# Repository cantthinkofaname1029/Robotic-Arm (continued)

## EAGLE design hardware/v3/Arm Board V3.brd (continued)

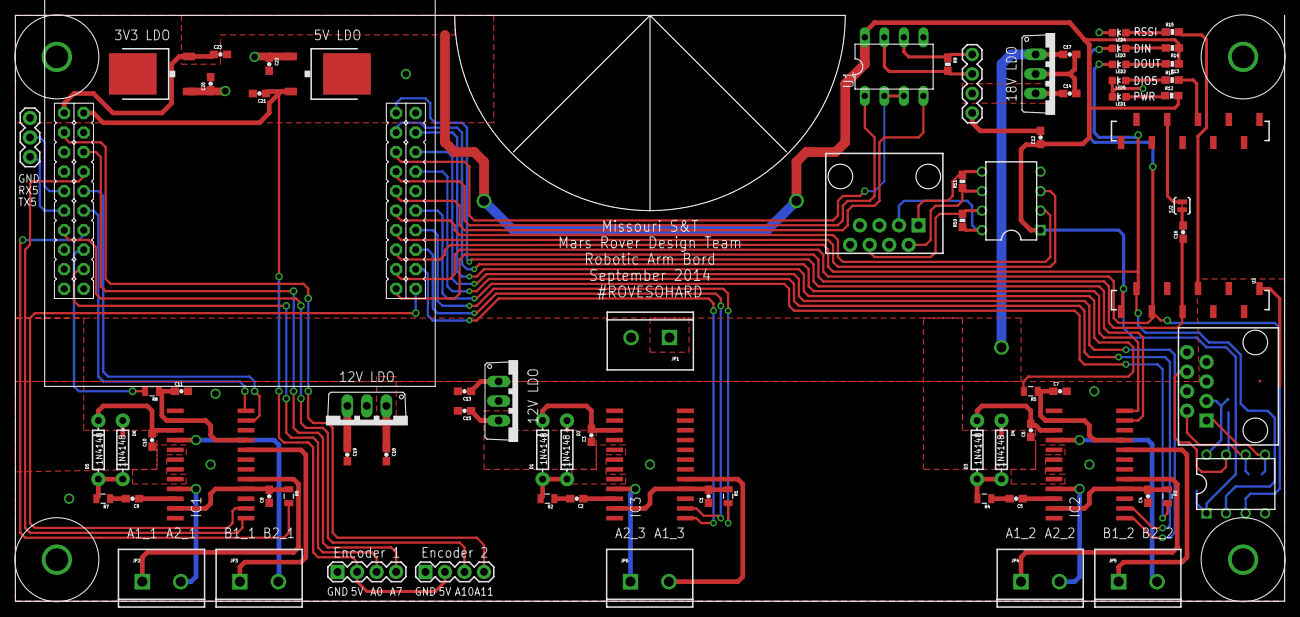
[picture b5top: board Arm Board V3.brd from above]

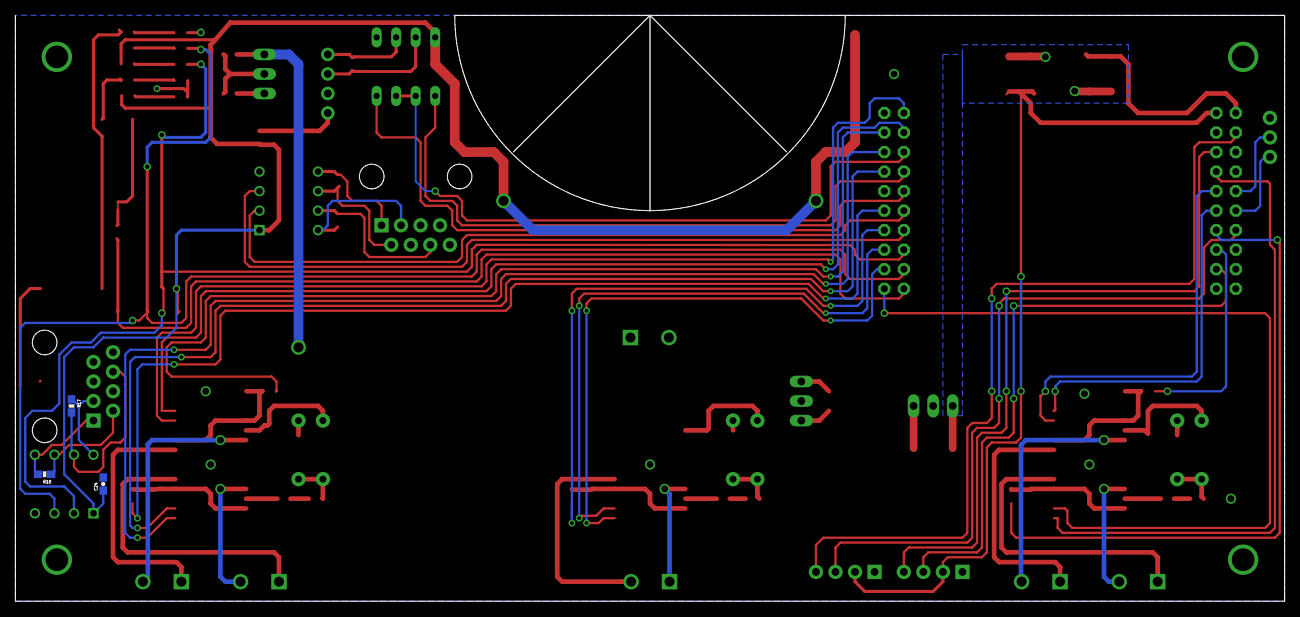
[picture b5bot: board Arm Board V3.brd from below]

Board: 2 copper layers, 165.1 x 76.2 mm, 83 parts (3 on the bottom side), 82 nets.

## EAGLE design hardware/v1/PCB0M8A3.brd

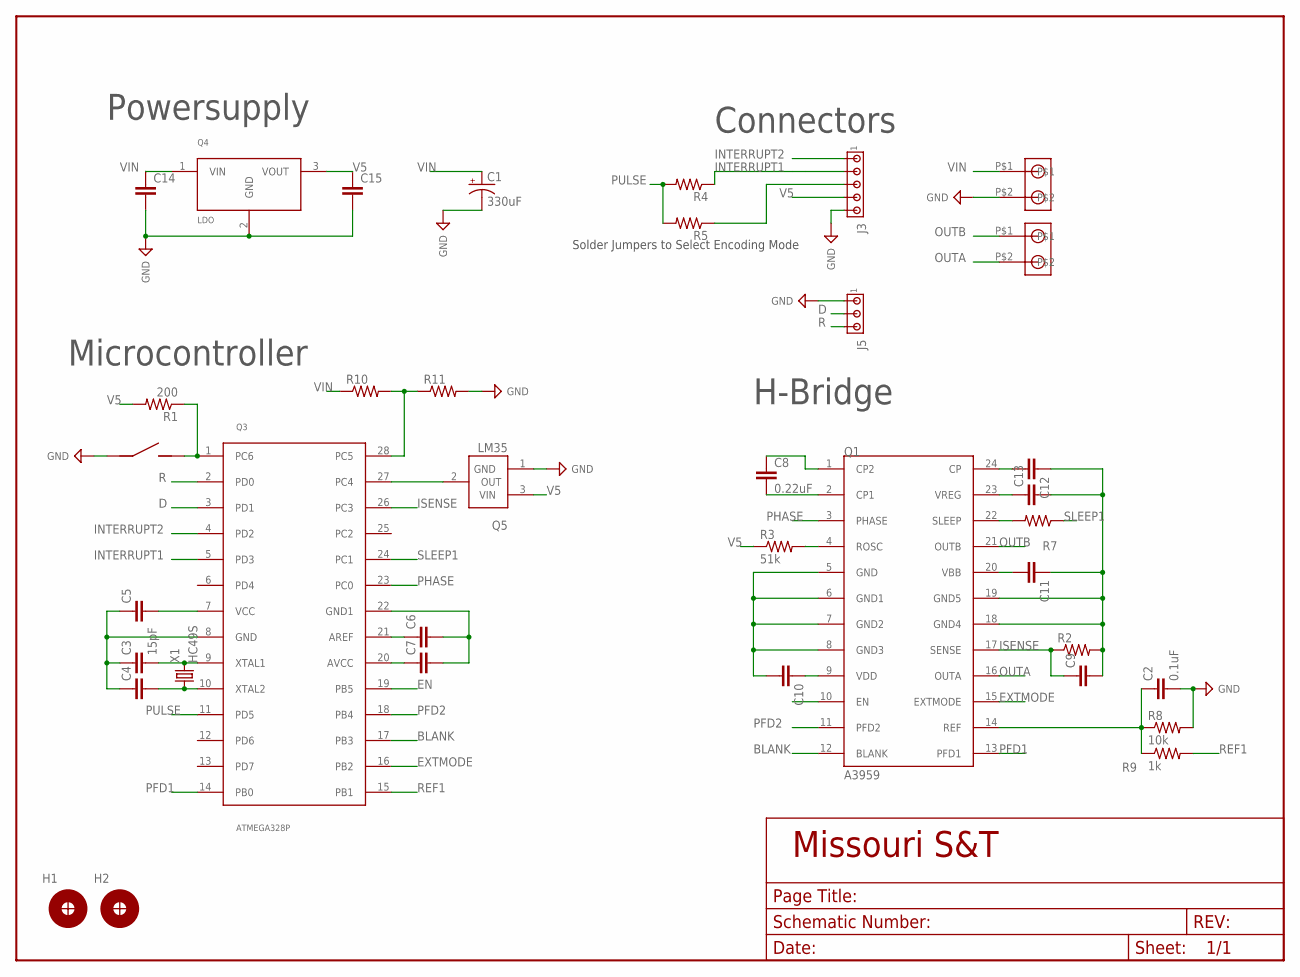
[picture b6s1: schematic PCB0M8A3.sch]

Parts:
C1: 330uF; C_8MM
C2: 0.1uF; C_0805
C3: 15pF; C_0805
C4, C5, C6, C7, C9, C10, C11, C12, C13, C14, C15: C_CAP_0805; C_0805
C8: 0.22uF; C_0805
H1, H2: H_MNTHOLE_#4
J1, J2: J_1546074-2282834-2; J_2.54MM
J3: J_MTA5P_100; J_MTA100_5P
J4: J_MC32857; J_TOGGLE
J5: J_MTA3P_100; J_MTA100_3P
Q1: A3959; DIP24
Q3: ATMEGA328P; DIP28
Q4: LDO; TO-220
Q5: LM35; TO-92-3
R1: 200; R_0805
R2: R_RES_2010; R_2010
R3: 51k; R_0805
R4, R5: R_RES_0603; R_0603
R7: R_1/4WL
R8: 10k; R_0805
R9: 1k; R_0805
R10, R11: R_RES_0805; R_0805
X1: HC49S; HC-49

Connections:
BLANK: Q1.12 (BLANK), Q3.17 (PB3)
D: J5.2, Q3.3 (PD1)
EN: Q1.10 (EN), Q3.19 (PB5)
EXTMODE: Q1.15 (EXTMODE), Q3.16 (PB2)
GND: C1.-, C2.2, C3.1, C4.1, C5.1, C6.2, C7.2, C9.2, C10.2, C11.1, C12.1, C13.2, C14.2, C15.2, J1.P$2, J3.5, J4.P$1 (1), J5.1, Q1.5 (GND), Q1.6 (GND1), Q1.7 (GND2), Q1.8 (GND3), Q1.18 (GND4), Q1.19 (GND5), Q3.8 (GND), Q3.22 (GND1), Q4.2 (GND), Q5.1 (GND), R2.2, R8.2, R11.2
INTERRUPT1: J3.2, Q3.5 (PD3), R4.1
INTERRUPT2: J3.1, Q3.4 (PD2)
ISENSE: C9.1, Q1.17 (SENSE), Q3.26 (PC3), R2.1
unnamed: C4.2, Q3.10 (XTAL2), X1.P$1 (1)
unnamed: C3.2, Q3.9 (XTAL1), X1.P$2 (2)
unnamed: Q1.22 (SLEEP), R7.2
unnamed: Q3.27 (PC4), Q5.2 (OUT)
unnamed: Q3.28 (PC5), R10.2, R11.1
unnamed: C6.1, Q3.21 (AREF)
unnamed: J3.3, R5.1
unnamed: J4.P$2 (2), Q3.1 (PC6), R1.1
unnamed: C8.1, Q1.1 (CP2)
unnamed: C8.2, Q1.2 (CP1)
unnamed: Q1.4 (ROSC), R3.2
unnamed: C12.2, Q1.24 (CP)
unnamed: C13.1, Q1.23 (VREG)
OUTA: J2.P$2, Q1.16 (OUTA)
OUTB: J2.P$1, Q1.21 (OUTB)
PFD1: Q1.13 (PFD1), Q3.14 (PB0)
PFD2: Q1.11 (PFD2), Q3.18 (PB4)
PHASE: Q1.3 (PHASE), Q3.23 (PC0)
PULSE: Q3.11 (PD5), R4.2, R5.2
R: J5.3, Q3.2 (PD0)
REF: C2.1, Q1.14 (REF), R8.1, R9.1
REF1: Q3.15 (PB1), R9.2
SLEEP1: Q3.24 (PC1), R7.1
V5: C5.2, C7.1, C10.1, C15.1, J3.4, Q1.9 (VDD), Q3.7 (VCC), Q3.20 (AVCC), Q4.3 (VOUT), Q5.3 (VIN), R1.2, R3.1
VIN: C1.+, C11.2, C14.1, J1.P$1, Q1.20 (VBB), Q4.1 (VIN), R10.1

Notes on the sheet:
Powersupply
Connectors
Microcontroller
H-Bridge
Solder Jumpers to Select Encoding Mode

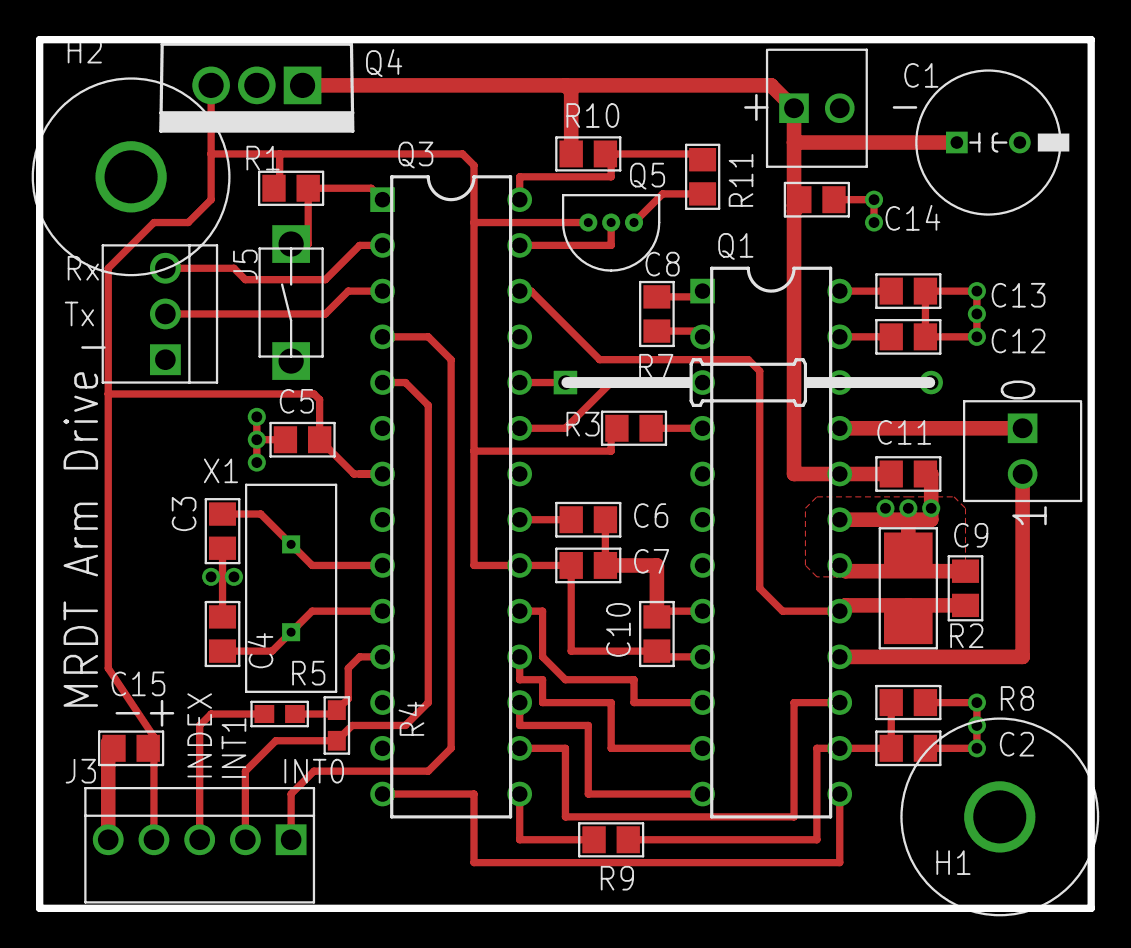
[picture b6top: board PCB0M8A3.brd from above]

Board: 2 copper layers, 58.4 x 48.3 mm, 37 parts (0 on the bottom side), 33 nets.

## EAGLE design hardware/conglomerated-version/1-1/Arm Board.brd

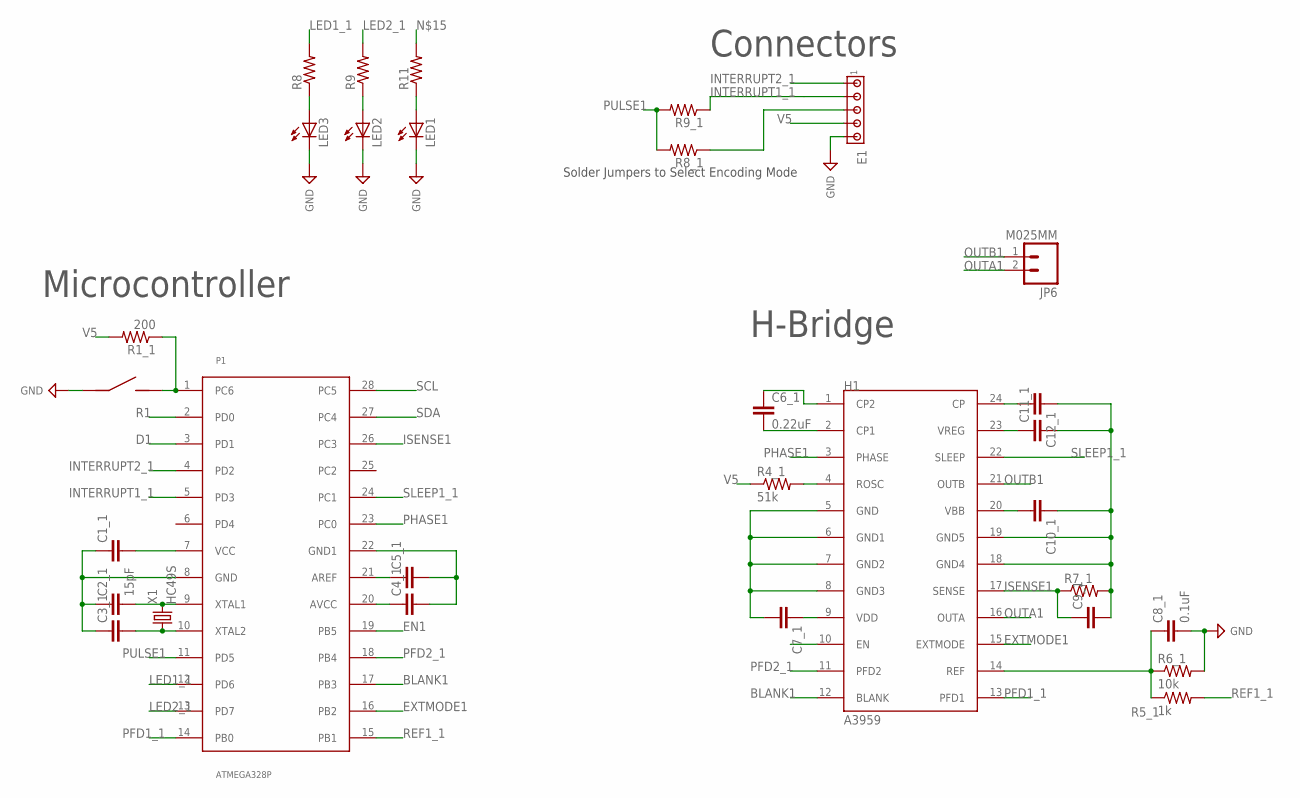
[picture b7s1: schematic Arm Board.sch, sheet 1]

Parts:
C1_1, C3_1, C4_1, C5_1, C7_1, C9_1, C10_1, C11_1, C12_1: C_CAP_0805; C_0805
C2_1: 15pF; C_0805
C6_1: 0.22uF; C_0805
C8_1: 0.1uF; C_0805
E1: J_MTA5P_100; J_MTA100_5P
H1: A3959; DIP24
JP6: M025MM; SCREWTERMINAL-5MM-2
LED1, LED2, LED3: LED1206; LED-1206
P1: ATMEGA328P; DIP28
R1_1: 200; R_0805
R4_1: 51k; R_0805
R5_1: 1k; R_0805
R6_1: 10k; R_0805
R7_1: R_RES_2010; R_2010
R8, R9, R11: RESISTOR1206; 1206
R8_1, R9_1: R_RES_0603; R_0603
S1: J_MC32857; J_TOGGLE
X1: HC49S; HC-49

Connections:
BLANK1: H1.12 (BLANK), P1.17 (PB3)
D1: P1.3 (PD1)
EN1: H1.10 (EN), P1.19 (PB5)
EXTMODE1: H1.15 (EXTMODE), P1.16 (PB2)
GND: C1_1.1, C2_1.1, C3_1.1, C4_1.2, C5_1.2, C7_1.2, C8_1.2, C9_1.2, C10_1.1, C11_1.2, C12_1.1, E1.5, H1.5 (GND), H1.6 (GND1), H1.7 (GND2), H1.8 (GND3), H1.18 (GND4), H1.19 (GND5), LED1.C, LED2.C, LED3.C, P1.8 (GND), P1.22 (GND1), R6_1.2, R7_1.2, S1.P$1 (1); also elsewhere on the board
INTERRUPT1_1: E1.2, P1.5 (PD3), R9_1.1
INTERRUPT2_1: E1.1, P1.4 (PD2)
ISENSE1: C9_1.1, H1.17 (SENSE), P1.26 (PC3), R7_1.1
LED1_1: P1.12 (PD6), R8.2
LED2_1: P1.13 (PD7), R9.2
unnamed: LED3.A, R8.1
unnamed: LED2.A, R9.1
unnamed: LED1.A, R11.1
unnamed: C3_1.2, P1.10 (XTAL2), X1.P$1 (1)
unnamed: C2_1.2, P1.9 (XTAL1), X1.P$2 (2)
unnamed: C5_1.1, P1.21 (AREF)
unnamed: P1.1 (PC6), R1_1.1, R11.2, S1.P$2 (2)
unnamed: C6_1.1, H1.1 (CP2)
unnamed: C6_1.2, H1.2 (CP1)
unnamed: H1.4 (ROSC), R4_1.2
unnamed: C12_1.2, H1.24 (CP)
unnamed: C11_1.1, H1.23 (VREG)
unnamed: E1.3, R8_1.1
OUTA1: H1.16 (OUTA), JP6.2
OUTB1: H1.21 (OUTB), JP6.1
PFD1_1: H1.13 (PFD1), P1.14 (PB0)
PFD2_1: H1.11 (PFD2), P1.18 (PB4)
PHASE1: H1.3 (PHASE), P1.23 (PC0)
PULSE1: P1.11 (PD5), R8_1.2, R9_1.2
R1: P1.2 (PD0)
REF1: C8_1.1, H1.14 (REF), R5_1.1, R6_1.1
REF1_1: P1.15 (PB1), R5_1.2
SCL: P1.28 (PC5); also elsewhere on the board
SDA: P1.27 (PC4); also elsewhere on the board
SLEEP1_1: H1.22 (SLEEP), P1.24 (PC1)
V5: C1_1.2, C4_1.1, C7_1.1, E1.4, H1.9 (VDD), P1.7 (VCC), P1.20 (AVCC), R1_1.2, R4_1.1; also elsewhere on the board
VIN: C10_1.2, H1.20 (VBB); also elsewhere on the board

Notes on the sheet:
Connectors
Microcontroller
H-Bridge
Solder Jumpers to Select Encoding Mode

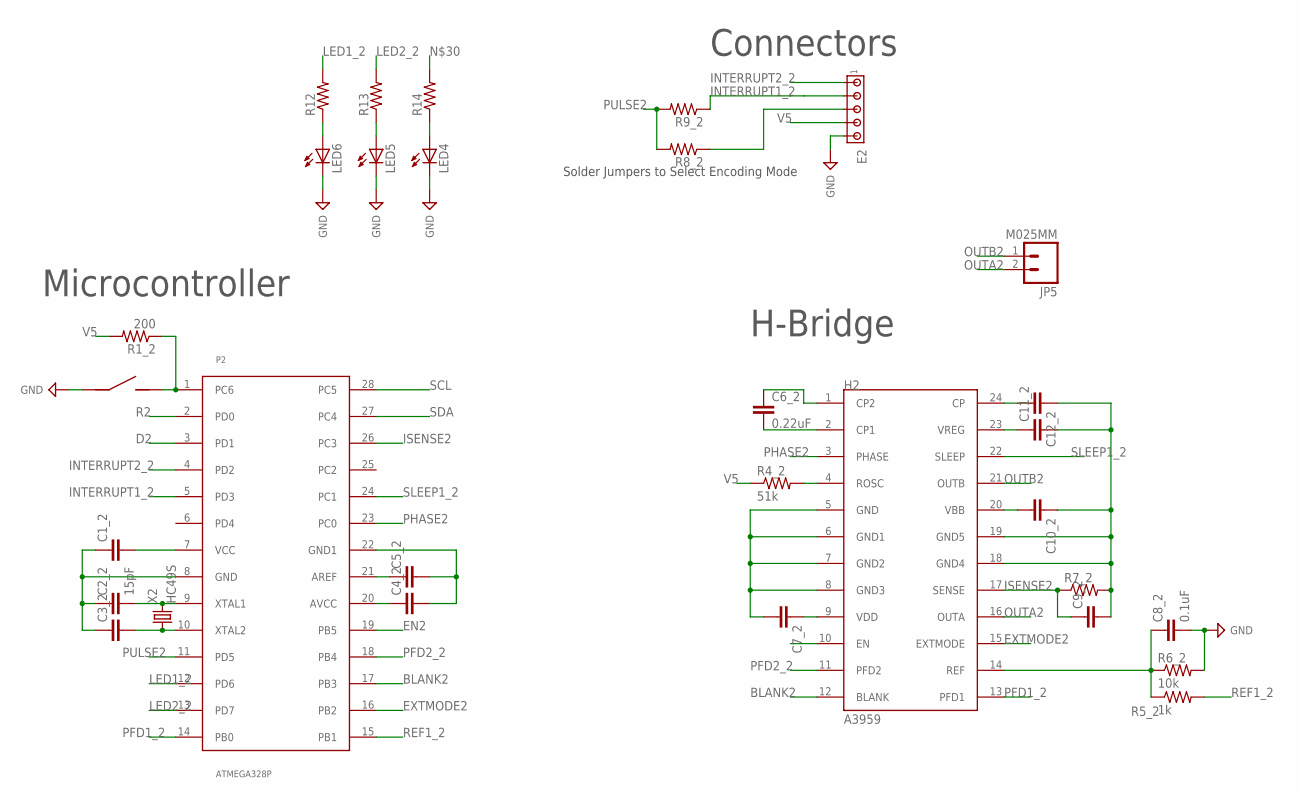
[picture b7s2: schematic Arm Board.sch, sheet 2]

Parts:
C1_2, C3_2, C4_2, C5_2, C7_2, C9_2, C10_2, C11_2, C12_2: C_CAP_0805; C_0805
C2_2: 15pF; C_0805
C6_2: 0.22uF; C_0805
C8_2: 0.1uF; C_0805
E2: J_MTA5P_100; J_MTA100_5P
H2: A3959; DIP24
JP5: M025MM; SCREWTERMINAL-5MM-2
LED4, LED5, LED6: LED1206; LED-1206
P2: ATMEGA328P; DIP28
R1_2: 200; R_0805
R4_2: 51k; R_0805
R5_2: 1k; R_0805
R6_2: 10k; R_0805
R7_2: R_RES_2010; R_2010
R8_2, R9_2: R_RES_0603; R_0603
R12, R13, R14: RESISTOR1206; 1206
S2: J_MC32857; J_TOGGLE
X2: HC49S; HC-49

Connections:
BLANK2: H2.12 (BLANK), P2.17 (PB3)
D2: P2.3 (PD1)
EN2: H2.10 (EN), P2.19 (PB5)
EXTMODE2: H2.15 (EXTMODE), P2.16 (PB2)
GND: C1_2.1, C2_2.1, C3_2.1, C4_2.2, C5_2.2, C7_2.2, C8_2.2, C9_2.2, C10_2.1, C11_2.2, C12_2.1, E2.5, H2.5 (GND), H2.6 (GND1), H2.7 (GND2), H2.8 (GND3), H2.18 (GND4), H2.19 (GND5), LED4.C, LED5.C, LED6.C, P2.8 (GND), P2.22 (GND1), R6_2.2, R7_2.2, S2.P$1 (1); also elsewhere on the board
INTERRUPT1_2: E2.2, P2.5 (PD3), R9_2.1
INTERRUPT2_2: E2.1, P2.4 (PD2)
ISENSE2: C9_2.1, H2.17 (SENSE), P2.26 (PC3), R7_2.1
LED1_2: P2.12 (PD6), R12.2
LED2_2: P2.13 (PD7), R13.2
unnamed: LED6.A, R12.1
unnamed: LED5.A, R13.1
unnamed: LED4.A, R14.1
unnamed: C3_2.2, P2.10 (XTAL2), X2.P$1 (1)
unnamed: C2_2.2, P2.9 (XTAL1), X2.P$2 (2)
unnamed: C5_2.1, P2.21 (AREF)
unnamed: P2.1 (PC6), R1_2.1, R14.2, S2.P$2 (2)
unnamed: C6_2.1, H2.1 (CP2)
unnamed: C6_2.2, H2.2 (CP1)
unnamed: H2.4 (ROSC), R4_2.2
unnamed: C12_2.2, H2.24 (CP)
unnamed: C11_2.1, H2.23 (VREG)
unnamed: E2.3, R8_2.1
OUTA2: H2.16 (OUTA), JP5.2
OUTB2: H2.21 (OUTB), JP5.1
PFD1_2: H2.13 (PFD1), P2.14 (PB0)
PFD2_2: H2.11 (PFD2), P2.18 (PB4)
PHASE2: H2.3 (PHASE), P2.23 (PC0)
PULSE2: P2.11 (PD5), R8_2.2, R9_2.2
R2: P2.2 (PD0)
REF1_2: P2.15 (PB1), R5_2.2
REF2: C8_2.1, H2.14 (REF), R5_2.1, R6_2.1
SCL: P2.28 (PC5); also elsewhere on the board
SDA: P2.27 (PC4); also elsewhere on the board
SLEEP1_2: H2.22 (SLEEP), P2.24 (PC1)
V5: C1_2.2, C4_2.1, C7_2.1, E2.4, H2.9 (VDD), P2.7 (VCC), P2.20 (AVCC), R1_2.2, R4_2.1; also elsewhere on the board
VIN: C10_2.2, H2.20 (VBB); also elsewhere on the board

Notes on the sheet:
Connectors
Microcontroller
H-Bridge
Solder Jumpers to Select Encoding Mode

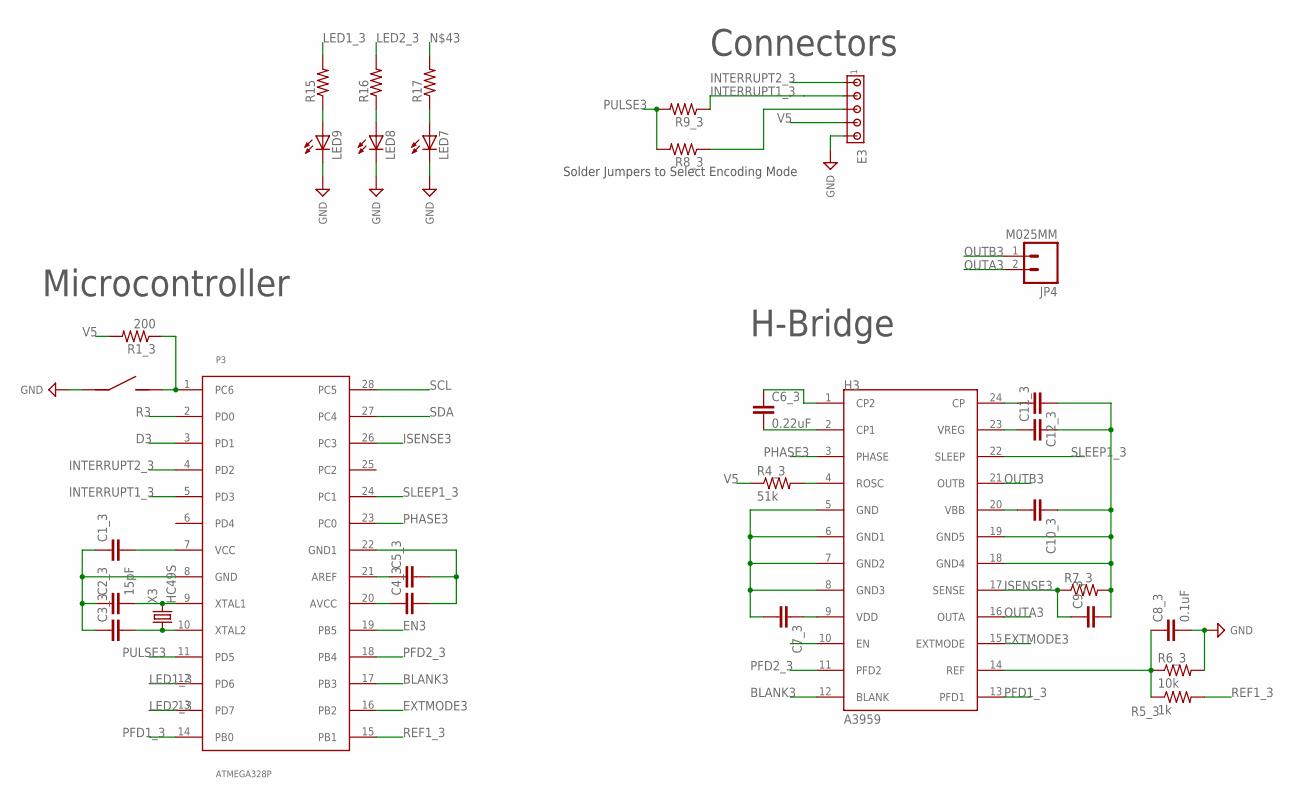
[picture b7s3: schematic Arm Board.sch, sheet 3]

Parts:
C1_3, C3_3, C4_3, C5_3, C7_3, C9_3, C10_3, C11_3, C12_3: C_CAP_0805; C_0805
C2_3: 15pF; C_0805
C6_3: 0.22uF; C_0805
C8_3: 0.1uF; C_0805
E3: J_MTA5P_100; J_MTA100_5P
H3: A3959; DIP24
JP4: M025MM; SCREWTERMINAL-5MM-2
LED7, LED8, LED9: LED1206; LED-1206
P3: ATMEGA328P; DIP28
R1_3: 200; R_0805
R4_3: 51k; R_0805
R5_3: 1k; R_0805
R6_3: 10k; R_0805
R7_3: R_RES_2010; R_2010
R8_3, R9_3: R_RES_0603; R_0603
R15, R16, R17: RESISTOR1206; 1206
S3: J_MC32857; J_TOGGLE
X3: HC49S; HC-49

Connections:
BLANK3: H3.12 (BLANK), P3.17 (PB3)
D3: P3.3 (PD1)
EN3: H3.10 (EN), P3.19 (PB5)
EXTMODE3: H3.15 (EXTMODE), P3.16 (PB2)
GND: C1_3.1, C2_3.1, C3_3.1, C4_3.2, C5_3.2, C7_3.2, C8_3.2, C9_3.2, C10_3.1, C11_3.2, C12_3.1, E3.5, H3.5 (GND), H3.6 (GND1), H3.7 (GND2), H3.8 (GND3), H3.18 (GND4), H3.19 (GND5), LED7.C, LED8.C, LED9.C, P3.8 (GND), P3.22 (GND1), R6_3.2, R7_3.2, S3.P$1 (1); also elsewhere on the board
INTERRUPT1_3: E3.2, P3.5 (PD3), R9_3.1
INTERRUPT2_3: E3.1, P3.4 (PD2)
ISENSE3: C9_3.1, H3.17 (SENSE), P3.26 (PC3), R7_3.1
LED1_3: P3.12 (PD6), R15.2
LED2_3: P3.13 (PD7), R16.2
unnamed: LED9.A, R15.1
unnamed: LED8.A, R16.1
unnamed: LED7.A, R17.1
unnamed: C3_3.2, P3.10 (XTAL2), X3.P$1 (1)
unnamed: C2_3.2, P3.9 (XTAL1), X3.P$2 (2)
unnamed: C5_3.1, P3.21 (AREF)
unnamed: P3.1 (PC6), R1_3.1, R17.2, S3.P$2 (2)
unnamed: C6_3.1, H3.1 (CP2)
unnamed: C6_3.2, H3.2 (CP1)
unnamed: H3.4 (ROSC), R4_3.2
unnamed: C12_3.2, H3.24 (CP)
unnamed: C11_3.1, H3.23 (VREG)
unnamed: E3.3, R8_3.1
OUTA3: H3.16 (OUTA), JP4.2
OUTB3: H3.21 (OUTB), JP4.1
PFD1_3: H3.13 (PFD1), P3.14 (PB0)
PFD2_3: H3.11 (PFD2), P3.18 (PB4)
PHASE3: H3.3 (PHASE), P3.23 (PC0)
PULSE3: P3.11 (PD5), R8_3.2, R9_3.2
R3: P3.2 (PD0)
REF1_3: P3.15 (PB1), R5_3.2
REF3: C8_3.1, H3.14 (REF), R5_3.1, R6_3.1
SCL: P3.28 (PC5); also elsewhere on the board
SDA: P3.27 (PC4); also elsewhere on the board
SLEEP1_3: H3.22 (SLEEP), P3.24 (PC1)
V5: C1_3.2, C4_3.1, C7_3.1, E3.4, H3.9 (VDD), P3.7 (VCC), P3.20 (AVCC), R1_3.2, R4_3.1; also elsewhere on the board
VIN: C10_3.2, H3.20 (VBB); also elsewhere on the board

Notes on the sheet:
Connectors
Microcontroller
H-Bridge
Solder Jumpers to Select Encoding Mode

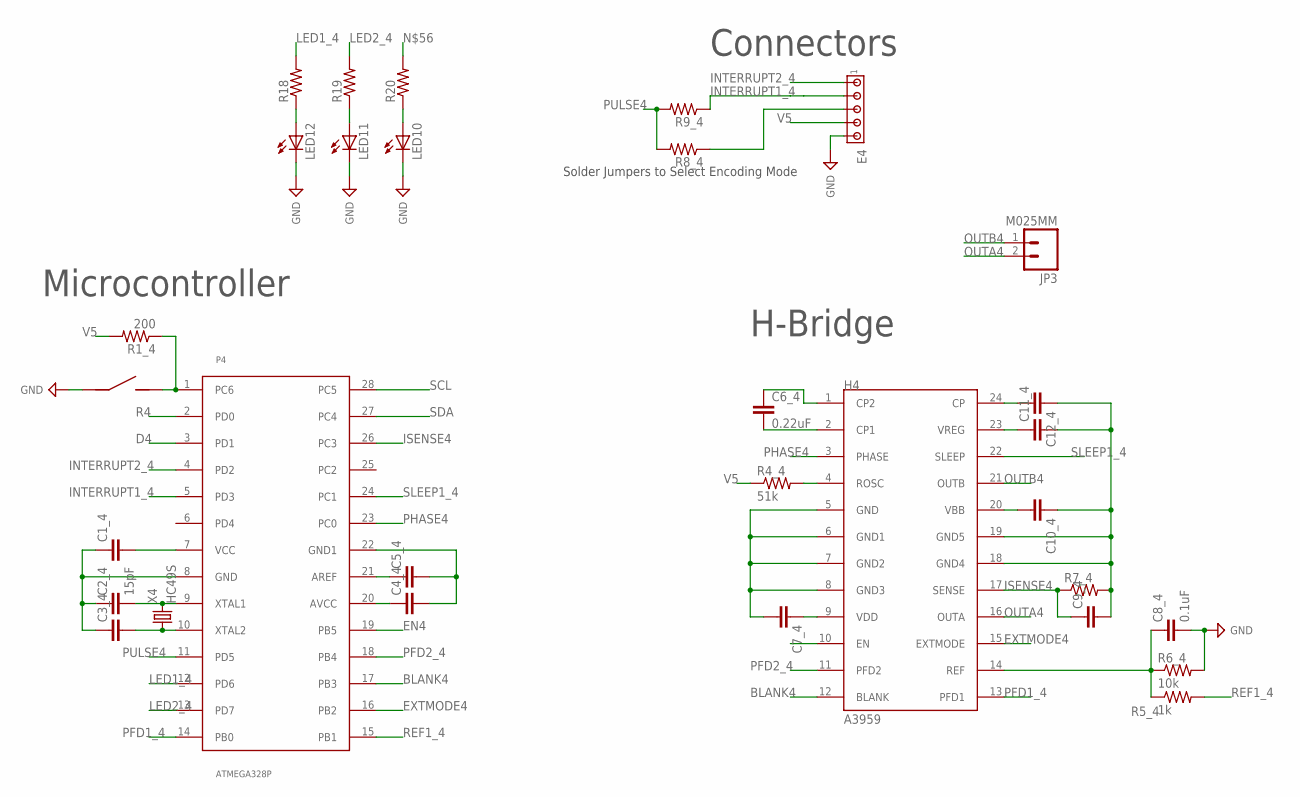
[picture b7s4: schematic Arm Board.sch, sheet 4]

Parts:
C1_4, C3_4, C4_4, C5_4, C7_4, C9_4, C10_4, C11_4, C12_4: C_CAP_0805; C_0805
C2_4: 15pF; C_0805
C6_4: 0.22uF; C_0805
C8_4: 0.1uF; C_0805
E4: J_MTA5P_100; J_MTA100_5P
H4: A3959; DIP24
JP3: M025MM; SCREWTERMINAL-5MM-2
LED10, LED11, LED12: LED1206; LED-1206
P4: ATMEGA328P; DIP28
R1_4: 200; R_0805
R4_4: 51k; R_0805
R5_4: 1k; R_0805
R6_4: 10k; R_0805
R7_4: R_RES_2010; R_2010
R8_4, R9_4: R_RES_0603; R_0603
R18, R19, R20: RESISTOR1206; 1206
S4: J_MC32857; J_TOGGLE
X4: HC49S; HC-49

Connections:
BLANK4: H4.12 (BLANK), P4.17 (PB3)
D4: P4.3 (PD1)
EN4: H4.10 (EN), P4.19 (PB5)
EXTMODE4: H4.15 (EXTMODE), P4.16 (PB2)
GND: C1_4.1, C2_4.1, C3_4.1, C4_4.2, C5_4.2, C7_4.2, C8_4.2, C9_4.2, C10_4.1, C11_4.2, C12_4.1, E4.5, H4.5 (GND), H4.6 (GND1), H4.7 (GND2), H4.8 (GND3), H4.18 (GND4), H4.19 (GND5), LED10.C, LED11.C, LED12.C, P4.8 (GND), P4.22 (GND1), R6_4.2, R7_4.2, S4.P$1 (1); also elsewhere on the board
INTERRUPT1_4: E4.2, P4.5 (PD3), R9_4.1
INTERRUPT2_4: E4.1, P4.4 (PD2)
ISENSE4: C9_4.1, H4.17 (SENSE), P4.26 (PC3), R7_4.1
LED1_4: P4.12 (PD6), R18.2
LED2_4: P4.13 (PD7), R19.2
unnamed: LED12.A, R18.1
unnamed: LED11.A, R19.1
unnamed: LED10.A, R20.1
unnamed: C3_4.2, P4.10 (XTAL2), X4.P$1 (1)
unnamed: C2_4.2, P4.9 (XTAL1), X4.P$2 (2)
unnamed: C5_4.1, P4.21 (AREF)
unnamed: P4.1 (PC6), R1_4.1, R20.2, S4.P$2 (2)
unnamed: C6_4.1, H4.1 (CP2)
unnamed: C6_4.2, H4.2 (CP1)
unnamed: H4.4 (ROSC), R4_4.2
unnamed: C12_4.2, H4.24 (CP)
unnamed: C11_4.1, H4.23 (VREG)
unnamed: E4.3, R8_4.1
OUTA4: H4.16 (OUTA), JP3.2
OUTB4: H4.21 (OUTB), JP3.1
PFD1_4: H4.13 (PFD1), P4.14 (PB0)
PFD2_4: H4.11 (PFD2), P4.18 (PB4)
PHASE4: H4.3 (PHASE), P4.23 (PC0)
PULSE4: P4.11 (PD5), R8_4.2, R9_4.2
R4: P4.2 (PD0)
REF1_4: P4.15 (PB1), R5_4.2
REF4: C8_4.1, H4.14 (REF), R5_4.1, R6_4.1
SCL: P4.28 (PC5); also elsewhere on the board
SDA: P4.27 (PC4); also elsewhere on the board
SLEEP1_4: H4.22 (SLEEP), P4.24 (PC1)
V5: C1_4.2, C4_4.1, C7_4.1, E4.4, H4.9 (VDD), P4.7 (VCC), P4.20 (AVCC), R1_4.2, R4_4.1; also elsewhere on the board
VIN: C10_4.2, H4.20 (VBB); also elsewhere on the board

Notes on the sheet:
Connectors
Microcontroller
H-Bridge
Solder Jumpers to Select Encoding Mode

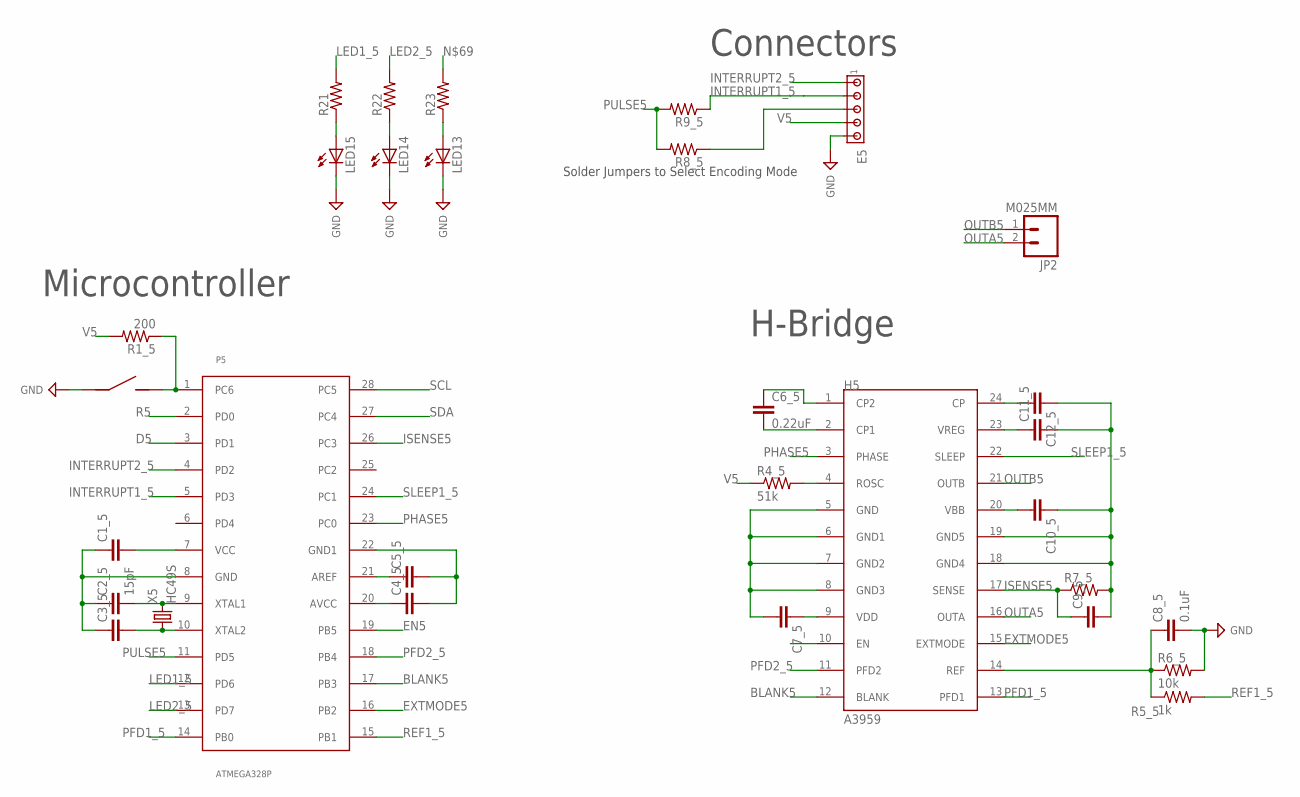
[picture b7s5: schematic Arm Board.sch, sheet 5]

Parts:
C1_5, C3_5, C4_5, C5_5, C7_5, C9_5, C10_5, C11_5, C12_5: C_CAP_0805; C_0805
C2_5: 15pF; C_0805
C6_5: 0.22uF; C_0805
C8_5: 0.1uF; C_0805
E5: J_MTA5P_100; J_MTA100_5P
H5: A3959; DIP24
JP2: M025MM; SCREWTERMINAL-5MM-2
LED13, LED14, LED15: LED1206; LED-1206
P5: ATMEGA328P; DIP28
R1_5: 200; R_0805
R4_5: 51k; R_0805
R5_5: 1k; R_0805
R6_5: 10k; R_0805
R7_5: R_RES_2010; R_2010
R8_5, R9_5: R_RES_0603; R_0603
R21, R22, R23: RESISTOR1206; 1206
S5: J_MC32857; J_TOGGLE
X5: HC49S; HC-49

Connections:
BLANK5: H5.12 (BLANK), P5.17 (PB3)
D5: P5.3 (PD1)
EN5: H5.10 (EN), P5.19 (PB5)
EXTMODE5: H5.15 (EXTMODE), P5.16 (PB2)
GND: C1_5.1, C2_5.1, C3_5.1, C4_5.2, C5_5.2, C7_5.2, C8_5.2, C9_5.2, C10_5.1, C11_5.2, C12_5.1, E5.5, H5.5 (GND), H5.6 (GND1), H5.7 (GND2), H5.8 (GND3), H5.18 (GND4), H5.19 (GND5), LED13.C, LED14.C, LED15.C, P5.8 (GND), P5.22 (GND1), R6_5.2, R7_5.2, S5.P$1 (1); also elsewhere on the board
INTERRUPT1_5: E5.2, P5.5 (PD3), R9_5.1
INTERRUPT2_5: E5.1, P5.4 (PD2)
ISENSE5: C9_5.1, H5.17 (SENSE), P5.26 (PC3), R7_5.1
LED1_5: P5.12 (PD6), R21.2
LED2_5: P5.13 (PD7), R22.2
unnamed: LED15.A, R21.1
unnamed: LED14.A, R22.1
unnamed: LED13.A, R23.1
unnamed: C3_5.2, P5.10 (XTAL2), X5.P$1 (1)
unnamed: C2_5.2, P5.9 (XTAL1), X5.P$2 (2)
unnamed: C5_5.1, P5.21 (AREF)
unnamed: P5.1 (PC6), R1_5.1, R23.2, S5.P$2 (2)
unnamed: C6_5.1, H5.1 (CP2)
unnamed: C6_5.2, H5.2 (CP1)
unnamed: H5.4 (ROSC), R4_5.2
unnamed: C12_5.2, H5.24 (CP)
unnamed: C11_5.1, H5.23 (VREG)
unnamed: E5.3, R8_5.1
OUTA5: H5.16 (OUTA), JP2.2
OUTB5: H5.21 (OUTB), JP2.1
PFD1_5: H5.13 (PFD1), P5.14 (PB0)
PFD2_5: H5.11 (PFD2), P5.18 (PB4)
PHASE5: H5.3 (PHASE), P5.23 (PC0)
PULSE5: P5.11 (PD5), R8_5.2, R9_5.2
R5: P5.2 (PD0)
REF1_5: P5.15 (PB1), R5_5.2
REF5: C8_5.1, H5.14 (REF), R5_5.1, R6_5.1
SCL: P5.28 (PC5); also elsewhere on the board
SDA: P5.27 (PC4); also elsewhere on the board
SLEEP1_5: H5.22 (SLEEP), P5.24 (PC1)
V5: C1_5.2, C4_5.1, C7_5.1, E5.4, H5.9 (VDD), P5.7 (VCC), P5.20 (AVCC), R1_5.2, R4_5.1; also elsewhere on the board
VIN: C10_5.2, H5.20 (VBB); also elsewhere on the board

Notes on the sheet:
Connectors
Microcontroller
H-Bridge
Solder Jumpers to Select Encoding Mode

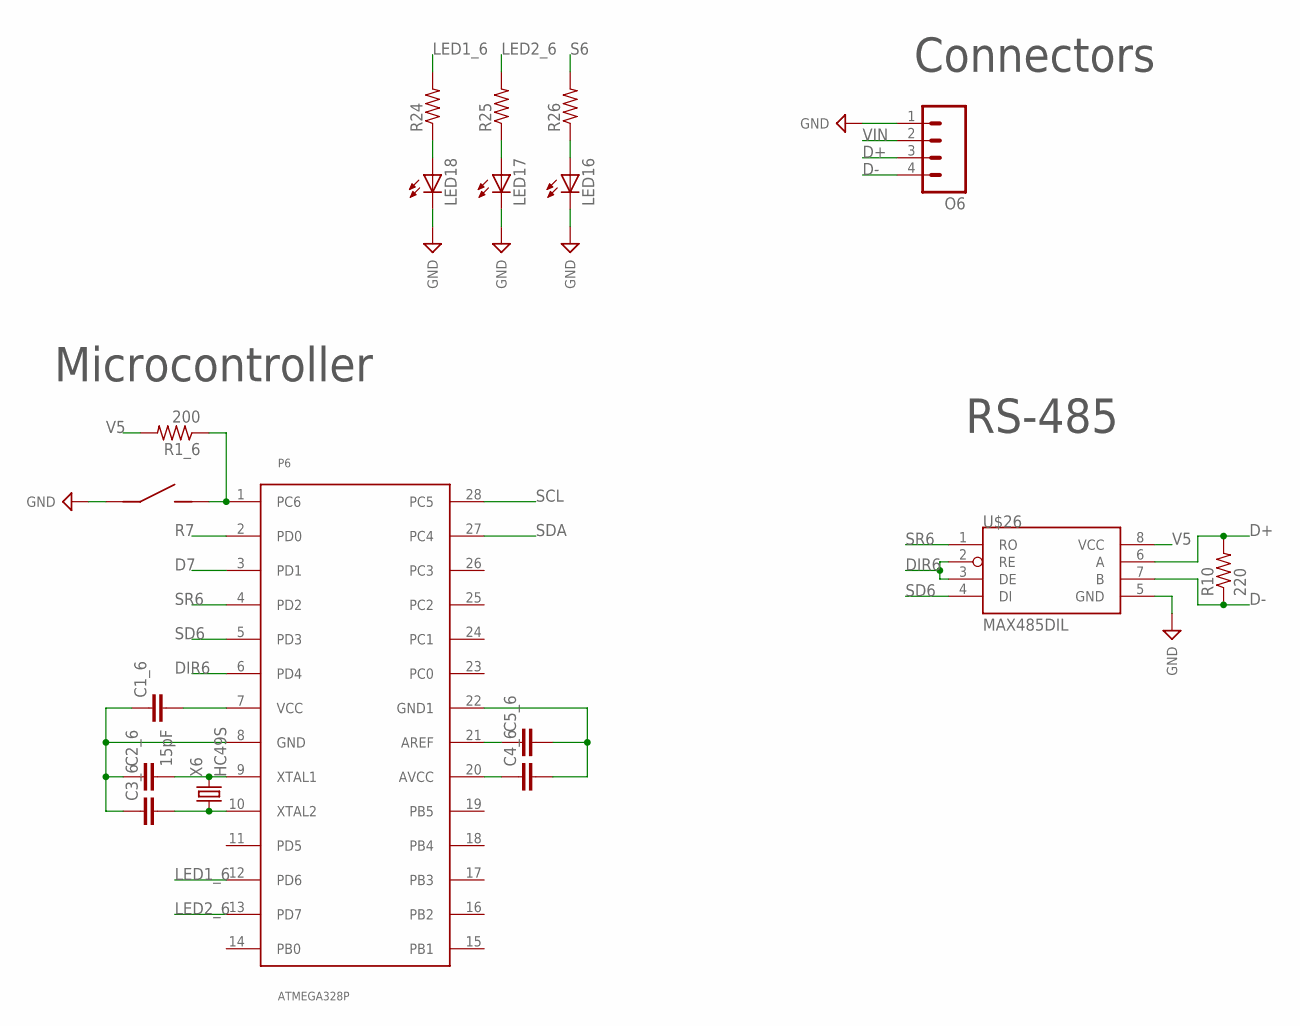
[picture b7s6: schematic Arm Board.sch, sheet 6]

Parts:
C1_6, C3_6, C4_6, C5_6: C_CAP_0805; C_0805
C2_6: 15pF; C_0805
J6: J_MC32857; J_TOGGLE
LED16, LED17, LED18: LED1206; LED-1206
O6: M041X04_NO_SILK; 1X04_NO_SILK
P6: ATMEGA328P; DIP28
R1_6: 200; R_0805
R10: 220; AXIAL-0.3EZ
R24, R25, R26: RESISTOR1206; 1206
U$26: MAX485DIL; DIL08
X6: HC49S; HC-49

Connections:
D7: P6.3 (PD1)
D+: O6.3, R10.P$2 (2), U$26.6 (A)
D-: O6.4, R10.P$1 (1), U$26.7 (B)
DIR6: P6.6 (PD4), U$26.2 (RE), U$26.3 (DE)
GND: C1_6.1, C2_6.1, C3_6.1, C4_6.2, C5_6.2, J6.P$1 (1), LED16.C, LED17.C, LED18.C, O6.1, P6.8 (GND), P6.22 (GND1), U$26.5 (GND); also elsewhere on the board
LED1_6: P6.12 (PD6), R24.2
LED2_6: P6.13 (PD7), R25.2
unnamed: LED18.A, R24.1
unnamed: LED17.A, R25.1
unnamed: LED16.A, R26.1
unnamed: C3_6.2, P6.10 (XTAL2), X6.P$1 (1)
unnamed: C2_6.2, P6.9 (XTAL1), X6.P$2 (2)
unnamed: C5_6.1, P6.21 (AREF)
R7: P6.2 (PD0)
S6: J6.P$2 (2), P6.1 (PC6), R1_6.1, R26.2
SCL: P6.28 (PC5); also elsewhere on the board
SD6: P6.5 (PD3), U$26.4 (DI)
SDA: P6.27 (PC4); also elsewhere on the board
SR6: P6.4 (PD2), U$26.1 (RO)
V5: C1_6.2, C4_6.1, P6.7 (VCC), P6.20 (AVCC), R1_6.2, U$26.8 (VCC); also elsewhere on the board
VIN: O6.2; also elsewhere on the board

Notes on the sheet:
Connectors
Microcontroller
RS-485

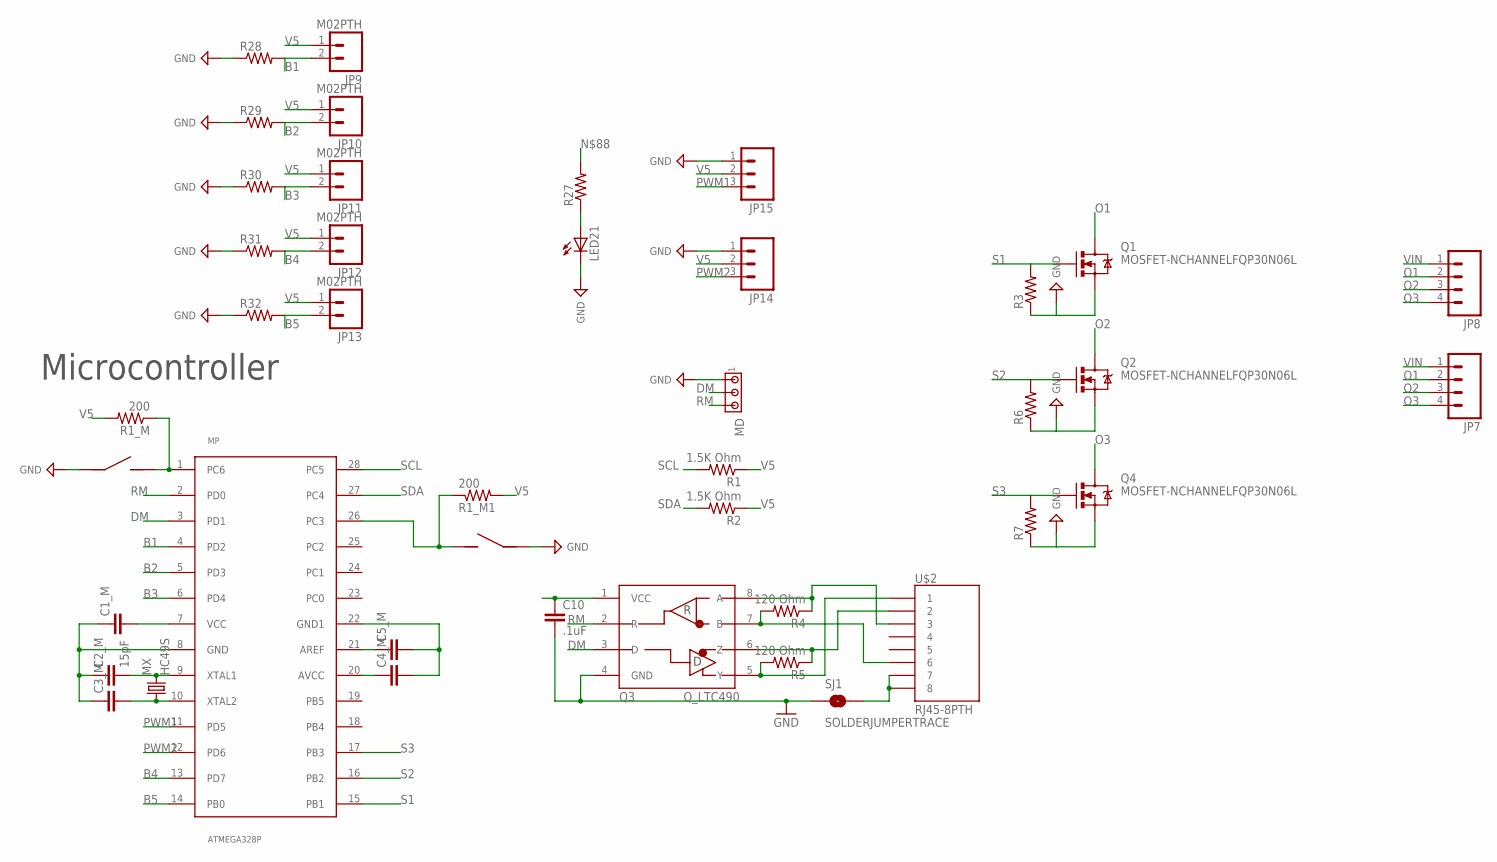
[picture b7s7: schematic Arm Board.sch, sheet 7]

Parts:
C1_M, C3_M, C4_M, C5_M: C_CAP_0805; C_0805
C2_M: 15pF; C_0805
C10: .1uF; CAP-PTH-SMALL-KIT
JP7, JP8: M041X04_NO_SILK; 1X04_NO_SILK
JP9, JP10, JP11, JP12, JP13: M02PTH; 1X02
JP14, JP15: M03PTH; 1X03
LED21: LED1206; LED-1206
MD: J_MTA3P_100; J_MTA100_3P
MP: ATMEGA328P; DIP28
MS, MS1: J_MC32857; J_TOGGLE
MX: HC49S; HC-49
Q1, Q2, Q4: MOSFET-NCHANNELFQP30N06L; TO220V
Q3: Q_LTC490; DIP8
R1, R2: 1.5K Ohm; AXIAL-0.3
R1_M, R1_M1: 200; R_0805
R3, R6, R7: 10KOHM1/6W5%(PTH)KIT; AXIAL-0.3-KIT
R4, R5: 120 Ohm; AXIAL-0.3
R27: RESISTOR1206; 1206
R28, R29, R30, R31, R32: RESISTORPTH-1/6W; 1/6W-RES
SJ1: SOLDERJUMPERTRACE; SJ_2S-TRACE
U$2: RJ45-8PTH; RJ45-8

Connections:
B1: JP9.2, MP.4 (PD2), R28.2
B2: JP10.2, MP.5 (PD3), R29.2
B3: JP11.2, MP.6 (PD4), R30.2
B4: JP12.2, MP.13 (PD7), R31.2
B5: JP13.2, MP.14 (PB0), R32.2
DM: MD.2, MP.3 (PD1), Q3.3 (D)
GND: C1_M.1, C2_M.1, C3_M.1, C4_M.2, C5_M.2, C10.2, JP14.1, JP15.1, LED21.C, MD.1, MP.8 (GND), MP.22 (GND1), MS.P$1 (1), MS1.P$1 (1), Q1.3 (S), Q2.3 (S), Q3.4 (GND), Q4.3 (S), R3.P$1 (1), R6.P$1 (1), R7.P$1 (1), R28.1, R29.1, R30.1, R31.1, R32.1, SJ1.1; also elsewhere on the board
unnamed: Q3.8 (A), R4.P$1 (1), U$2.3
unnamed: Q3.5 (Y), R5.P$2 (2), U$2.1
unnamed: SJ1.2, U$2.7, U$2.8
unnamed: Q3.6 (Z), R5.P$1 (1), U$2.2
unnamed: Q3.7 (B), R4.P$2 (2), U$2.6
unnamed: LED21.A, R27.1
unnamed: MP.26 (PC3), MS1.P$2 (2), R1_M1.1
unnamed: C3_M.2, MP.10 (XTAL2), MX.P$1 (1)
unnamed: C2_M.2, MP.9 (XTAL1), MX.P$2 (2)
unnamed: C5_M.1, MP.21 (AREF)
unnamed: MP.1 (PC6), MS.P$2 (2), R1_M.1, R27.2
O1: JP7.2, JP8.2, Q1.2 (D)
O2: JP7.3, JP8.3, Q2.2 (D)
O3: JP7.4, JP8.4, Q4.2 (D)
PWM1: JP15.3, MP.11 (PD5)
PWM2: JP14.3, MP.12 (PD6)
RM: MD.3, MP.2 (PD0), Q3.2 (R)
S1: MP.15 (PB1), Q1.1 (G), R3.P$2 (2)
S2: MP.16 (PB2), Q2.1 (G), R6.P$2 (2)
S3: MP.17 (PB3), Q4.1 (G), R7.P$2 (2)
SCL: MP.28 (PC5), R1.P$2 (2); also elsewhere on the board
SDA: MP.27 (PC4), R2.P$2 (2); also elsewhere on the board
V5: C1_M.2, C4_M.1, C10.1, JP9.1, JP10.1, JP11.1, JP12.1, JP13.1, JP14.2, JP15.2, MP.7 (VCC), MP.20 (AVCC), Q3.1 (VCC), R1.P$1 (1), R1_M.2, R1_M1.2, R2.P$1 (1); also elsewhere on the board
VIN: JP7.1, JP8.1; also elsewhere on the board

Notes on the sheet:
Microcontroller

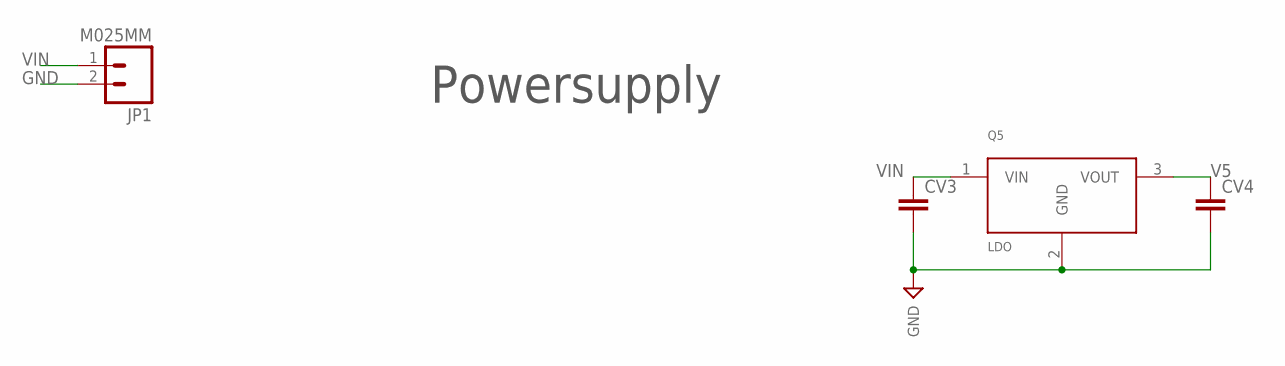
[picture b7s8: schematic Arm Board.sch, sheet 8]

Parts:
CV3, CV4: C_CAP_0805; C_0805
JP1: M025MM; SCREWTERMINAL-5MM-2
Q5: LDO; TO-220

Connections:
GND: CV3.2, CV4.2, JP1.2, Q5.2 (GND); also elsewhere on the board
V5: CV4.1, Q5.3 (VOUT); also elsewhere on the board
VIN: CV3.1, JP1.1, Q5.1 (VIN); also elsewhere on the board

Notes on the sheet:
Powersupply
